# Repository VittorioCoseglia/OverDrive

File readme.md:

# Pedal Overdrive TL071 🎛️

Un pedal de efectos para guitarra basado en el clásico circuito **[Ibanez Tube Screamer](https://es.wikipedia.org/wiki/Ibanez_Tube_Screamer)**. Permite controlar y variar el nivel de saturación de la señal de audio mediante el potenciómetro de *Drive*.

---

## 📋 Tabla de Contenidos
- [Características Principales](#-características-principales)
- [Lista de Materiales (BOM)](#-lista-de-materiales-bom)
- [Esquemático y PCB](#-esquemático-y-pcb)
- [Carcasa / Enclosure](#-carcasa--enclosure)
- [Software Utilizado](#-software-utilizado)

---

## 🚀 Características Principales

- **Controles:** Potenciómetro de *Drive* para ajustar el nivel de recortes/saturación.
- **Diseño de PCB:** Monocapa (*single-layer*) con tecnología de inserción **[THT](control-board/readme.md)**.
- **Carcasa:** Estructura modular apta para **impresión 3D** utilizando tornillería **M3**.

> [!WARNING]
> **Alimentación Eléctrica:** Este circuito requiere una fuente de alimentación de **9V DC con polaridad de centro negativo** ($\text{9V DC, Center-Negative}$), el estándar de pedales de efecto. Conectar una polaridad invertida puede dañar los componentes.

---

## 📦 Lista de Materiales (BOM)

Consulta la lista completa de componentes electrónicos y de hardware necesarios para el ensamblaje en el siguiente enlace:

📄 **[Ver Lista de Materiales (BOM)](docs/bom.md)**

---

## 📐 Esquemático y PCB

### Esquema Electrónico

### Diseño de la PCB
Diseñado en una sola capa (*Single Layer*) para facilitar el ruteado y el grabado casero o fabricación de bajo costo.

---

## 🧷 Carcasa (Case)

El chasis o carcasa está optimizado para su **impresión 3D** y diseñado para ensamblarse mediante tornillos roscados **M3**.

---

## 🛠️ Software Utilizado

| Herramienta | Uso / Función | Enlace |
| :--- | :--- | :--- |
| **KiCad 9.0** | Diseño del esquemático y PCB | [Sitio Oficial](https://www.kicad.org/) |
| **SolidWorks 2022** | Modelado 3D de la carcasa | [Sitio Oficial](https://www.solidworks.com/) |
| **NI Multisim 14.1** | Simulación de la respuesta del circuito | [Información](https://en.wikipedia.org/wiki/NI_Multisim) |

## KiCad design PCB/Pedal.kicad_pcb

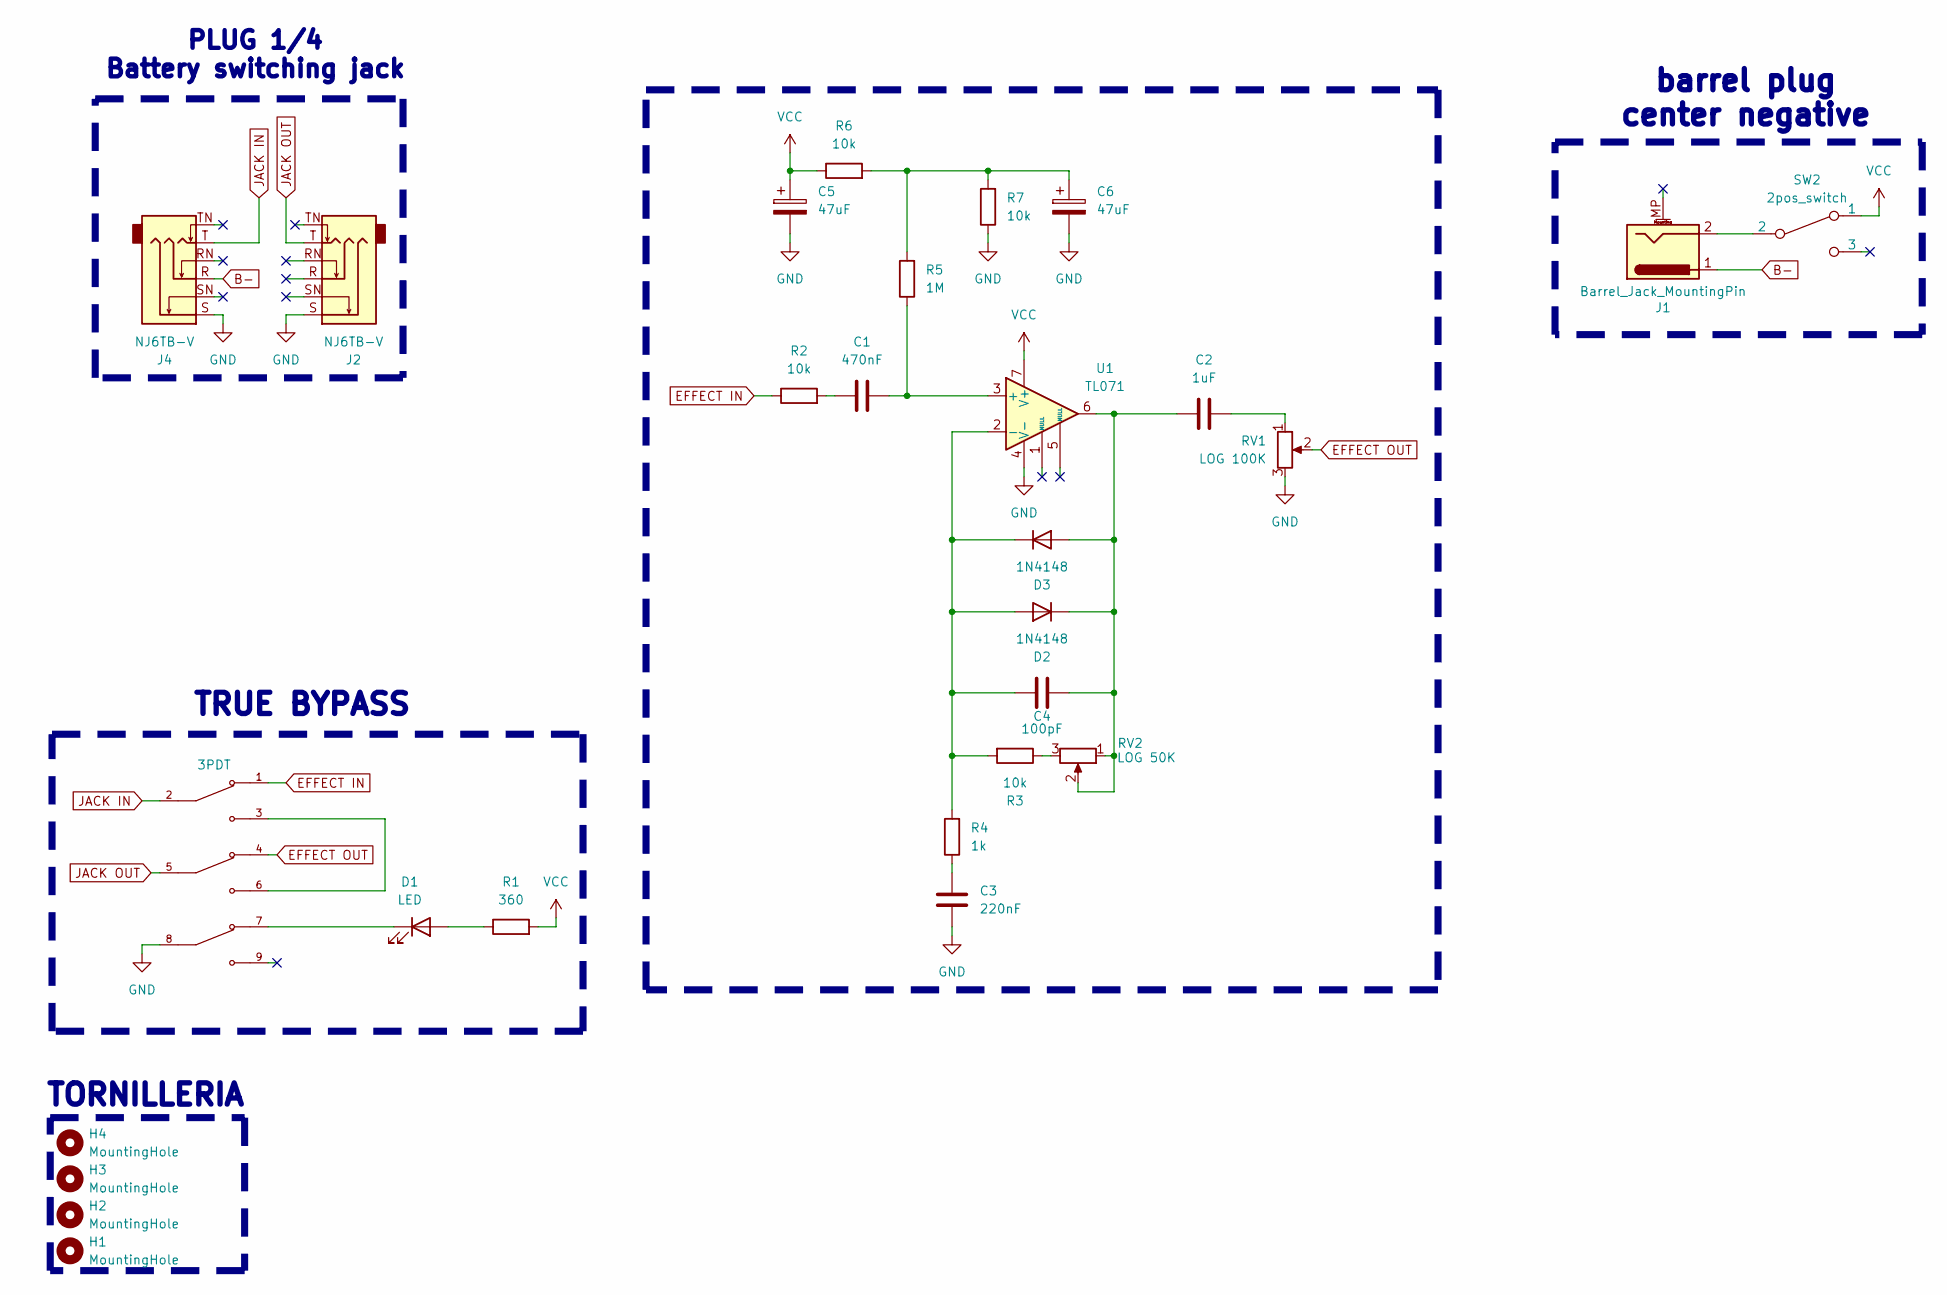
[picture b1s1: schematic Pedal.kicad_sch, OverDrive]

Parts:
3PDT2: 3PDT
C1: 470nF; C_Rect_L7.2mm_W3.0mm_P5.00mm_FKS2_FKP2_MKS2_MKP2
C2: 1uF; C_Rect_L7.2mm_W3.0mm_P5.00mm_FKS2_FKP2_MKS2_MKP2
C3: 220nF; C_Rect_L7.2mm_W2.5mm_P5.00mm_FKS2_FKP2_MKS2_MKP2
C4: 100pF; C_Disc_D3.0mm_W2.0mm_P2.50mm
C5, C6: 47uF; CP_Radial_D5.0mm_P2.00mm
D1: LED; LED_D5.0mm
D2, D3: 1N4148; D_DO-35_SOD27_P7.62mm_Horizontal
H1, H2, H3, H4: MountingHole; MountingHole_3.2mm_M3
J1: Barrel_Jack_MountingPin; DC_Power_Jack_PCB_Mounted_2.1mm
J2, J4: NJ6TB-V; Jack_6.35mm_Neutrik_NMJ6HFD4_Horizontal
R1: 360; R_Axial_DIN0207_L6.3mm_D2.5mm_P10.16mm_Horizontal
R2, R3, R6, R7: 10k; R_Axial_DIN0207_L6.3mm_D2.5mm_P10.16mm_Horizontal
R4: 1k; R_Axial_DIN0207_L6.3mm_D2.5mm_P10.16mm_Horizontal
R5: 1M; R_Axial_DIN0207_L6.3mm_D2.5mm_P10.16mm_Horizontal
RV1: LOG 100K; Potentiometer_Alps_RK163_Single_Horizontal
RV2: LOG 50K; Potentiometer_Alps_RK163_Single_Horizontal
SW2: 2pos_switch; SW_Slide_SPDT_Straight_CK_OS102011MS2Q
U1: TL071; DIP-8_W7.62mm_LongPads

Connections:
B-: J1.1, J4.R
EFFECT IN: 3PDT2.1, R2.1
EFFECT OUT: 3PDT2.4, RV1.2
GND: 3PDT2.8, C3.1, C5.2, C6.2, J2.S, J4.S, R7.1, RV1.3, U1.4 (V-)
JACK IN: 3PDT2.2, J4.T
JACK OUT: 3PDT2.5, J2.T
unnamed: 3PDT2.3, 3PDT2.6
unnamed: C1.1, R2.2
unnamed: C2.2, RV1.1
unnamed: C3.2, R4.1
unnamed: C6.1, R5.2, R6.2, R7.2
unnamed: D1.2 (A), R1.1
unnamed: 3PDT2.7, D1.1 (K)
unnamed: C4.1, D2.2 (A), D3.1 (K), R3.2, R4.2, U1.2 (-)
unnamed: C2.1, C4.2, D2.1 (K), D3.2 (A), RV2.1, RV2.2, U1.6
unnamed: J1.2, SW2.2
unnamed: R3.1, RV2.3
unnamed: C1.2, R5.1, U1.3 (+)
VCC: C5.1, R1.2, R6.1, SW2.1, U1.7 (V+)

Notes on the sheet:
barrel plug center negative
TORNILLERIA
PLUG 1/4 Battery switching jack
TRUE BYPASS

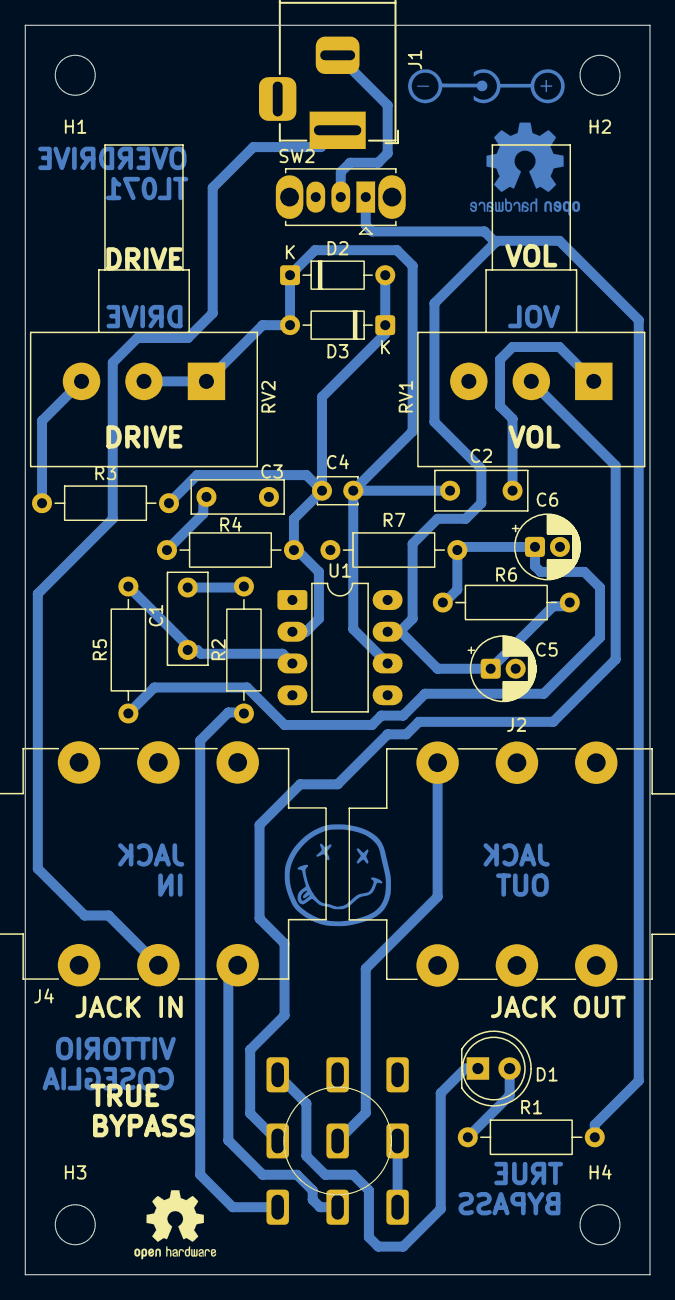
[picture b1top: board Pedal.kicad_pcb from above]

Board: 2 copper layers, 50.0 x 100.0 mm, 28 parts (0 on the bottom side), 19 nets.

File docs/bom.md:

# Bill of Materials 📑

> all of components are **THT**

_**The price factors in the quantity.**_
## Component List

| Reference | Qty | Value | Datasheet |
|---|---|---|---|
| 3PDT2 | 1 | 3PDT | |
| C1 | 1 | 470nF | |
| C2 | 1 | 1uF | |
| C3 | 1 | 220nF | |
| C4 | 1 | 100pF | |
| C5,C6 | 2 | 47uF | |
| D1 | 1 | LED | |
| D2,D3 | 2 | 1N4148 | [Datasheet](https://assets.nexperia.com/documents/data-sheet/1N4148_1N4448.pdf) |
| J1 | 1 | Barrel_Jack_MountingPin | |
| J2,J4 | 2 | NJ6TB-V | [Datasheet](https://www.neutrik.com/en/product/nj6tb-v) |
| R1 | 1 | 360 | |
| R2,R3,R6,R7 | 4 | 10k | |
| R4 | 1 | 1k | |
| R5 | 1 | 1M | |
| RV1 | 1 | LOG 100K | |
| RV2 | 1 | LOG 50K | |
| SW2 | 1 | 2pos_switch | [Datasheet](https://www.digikey.com/en/products/detail/c-k/OS102011MS2QS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 |
| U1 | 1 | TL071 | [Datasheet](http://www.ti.com/lit/ds/symlink/tl071.pdf) |
